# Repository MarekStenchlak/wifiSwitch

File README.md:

# wifiSwitch

## MQTT wifi wall switch using ESP8266-01

### Description
Switch can be controlled via **MQTT** or **touch button.**

it is well suited for 68mm Europe wall boxes.

Switch is based on wifi board [ESP8266-01](https://en.wikipedia.org/wiki/ESP8266).

Code is implemented in Arduino. Source files can be found in repository.

**This project requires 220V mains to operate properly**

**If you are not familiar with mains DO NOT TRY TO INSTALL THIS SWITCH**

**Proceed only if you know what you are doing !!!**

Board can be ordered on OSH park:
  https://oshpark.com/shared_projects/9JxnbNwu

### Schematics
Schematics for this project was designed using Eagle.

Eagle project can be found in repository.

### Board

### BOM (Bill Of Materials)
*TODO*

### 3D model
3D model was designed in Sketch-Up and exported to STL files.

Model consists of 3 parts: **box, frame and button cover.**

3D model files and exported STL files can be found in repository.

Exploded view looks like this:

## Setup

### Wiring
**Be sure you know what you are doing! Never touch any live wires ! Be sure to turn off electricity when dealing with mains!**

If you do not have **Neutral** wire in the wall box (which you probably don`t), you will have to wire new cable and connect it to **Neutral.**

### MQTT broker
To use this switch you need to have an MQTT broker like [Mosquitto](https://mosquitto.org/) installed on a server or RaspeberryPi in your local wifi network.

To install Mosquitto, please follow this guide: [Setup mosquitto MQTT broker](https://www.digitalocean.com/community/tutorials/how-to-install-and-secure-the-mosquitto-mqtt-messaging-broker-on-ubuntu-16-04)

or this guie for RaspberryPi: [Setup mosquitto MQTT broker on RPi](http://www.instructables.com/id/Installing-MQTT-BrokerMosquitto-on-Raspberry-Pi/)

The bast practise is to set static IP address to the MQTT broker server or raspberryPi running mosquitto.

### WifiSwitch settings
This switch is using [WifiManager](https://github.com/tzapu/WiFiManager) project to set-up switch parameters.

When the switch is connected to mains, it tries to connect to configured Wifi network and MQTT broker. If it is not able to connect or is not configured, it enters the configuration mode.

#### Configuration mode
  When in configuration mode, the switch creates its own wifi network.
  This network`s SSID consists of string "ESP_HOME" followed by its MAC address 
  
  e.g: ESP_HOME A1:B2:3A:4E:2D:E2
    
  This network has no Password.
  
  After you connect to this network (e.g using smartphone) enter IP address 
  
  **192.168.4.1**
  
  Then configure:
  
  wifi SSID
  
  wifi Password
  
  MQTT broker IP (or DNS name)
  
  MQTT broker port
  
  MQTT username
  
  MQTT password
  
  MQTT topic
    
## Final Product

### Assembled board

### Assembled switch

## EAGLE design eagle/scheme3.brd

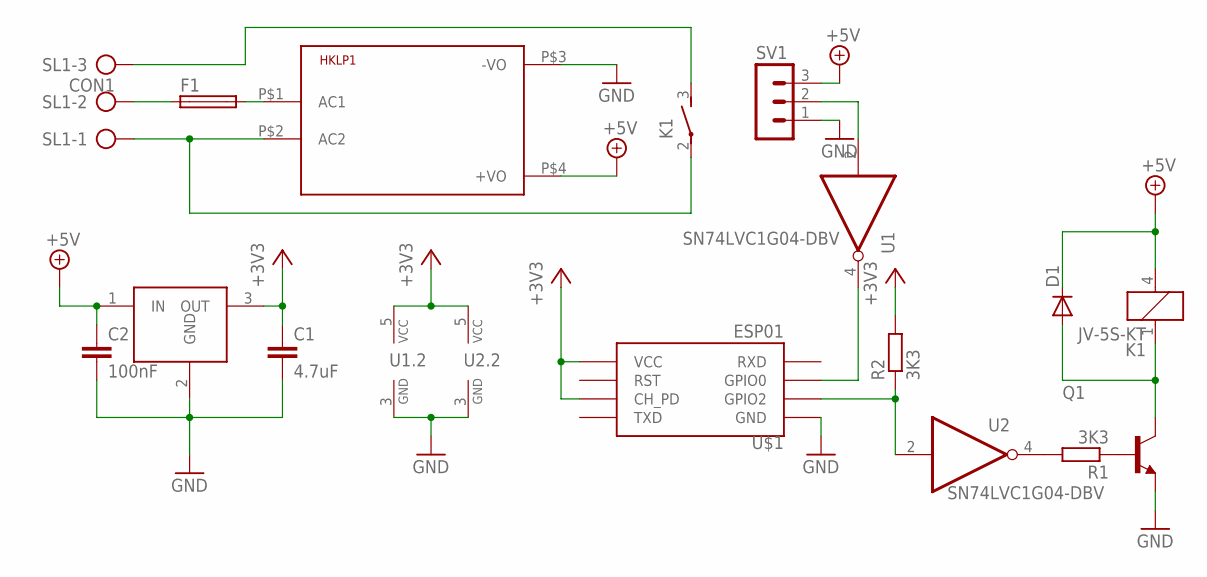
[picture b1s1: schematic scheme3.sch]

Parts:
C1: 4.7uF; C0805
C2: 100nF; C0603
D1: D-SOD123; SOD123
F1: TE5
HKLP1: HKLPM01
K1: JV-5S-KT; JV-KT
Q1: BC817-16-NPN-SOT23-BEC; SOT23-BEC
R1, R2: 3K3; R0603
SL1: CON1; AK300/3
SV1: MA03-1
U1, U2: SN74LVC1G04-DBV; SOT23-5
U$1: ESP01
U$2: LF33CV; TO220V

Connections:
+3V3: C1.1, R2.2, U1.5 (VCC), U2.5 (VCC), U$1.CH_PD, U$1.VCC, U$2.3 (OUT)
+5V: C2.1, D1.1 (C), HKLP1.P$4 (+VO), K1.4 (2), SV1.3, U$2.1 (IN)
GND: C1.2, C2.2, HKLP1.P$3 (-VO), Q1.E, SV1.1, U1.3 (GND), U2.3 (GND), U$1.GND, U$2.2 (GND)
unnamed: Q1.B, R1.1
unnamed: R2.1, U2.2 (A), U$1.GPIO2
unnamed: R1.2, U2.4 (Y)
unnamed: D1.2 (A), K1.1, Q1.C
unnamed: F1.1, SL1.2
unnamed: SV1.2, U1.2 (A)
unnamed: HKLP1.P$2 (AC2), K1.2, SL1.1
unnamed: K1.3 (S), SL1.3
unnamed: F1.2, HKLP1.P$1 (AC1)
unnamed: U1.4 (Y), U$1.GPIO0

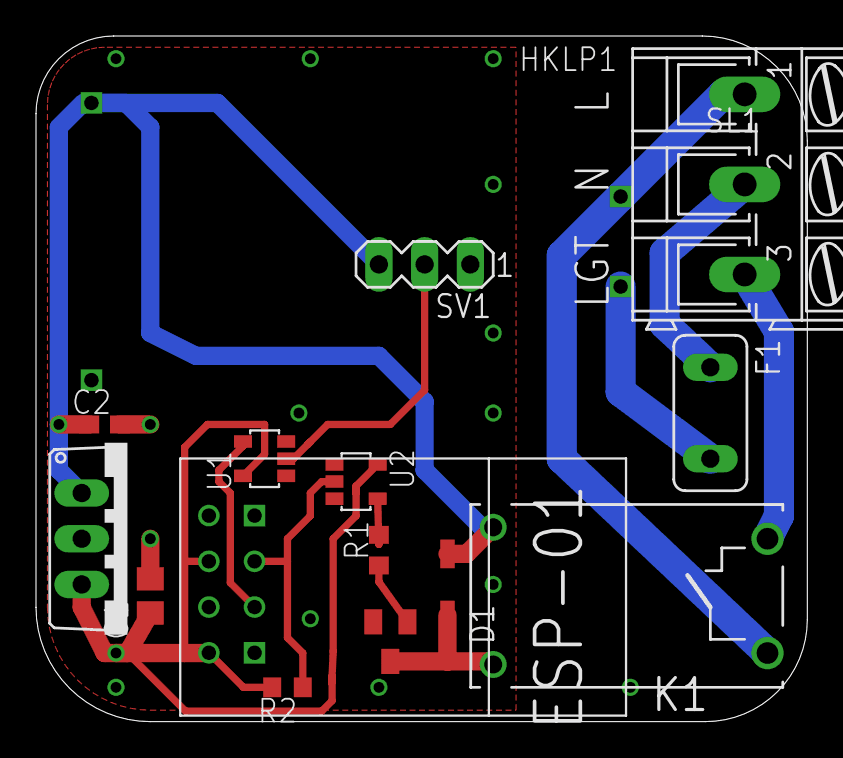
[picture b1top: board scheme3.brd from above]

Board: 2 copper layers, 42.9 x 38.1 mm, 15 parts (0 on the bottom side), 13 nets.

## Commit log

2018-02-05 Create LICENSE

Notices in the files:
parts and their libraries:
m-pad-2.1: License : GNU General Public License version 2 (see bottom)
